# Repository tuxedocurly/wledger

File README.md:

<div align="center">

</div>

> **The Ultimate Inventory Management System for Makers.**
> *Organize your electronic components and find them instantly with WLED.*

Check out the official WLEDger documentation site [here](https://tuxedocurly.github.io/wledger/)
## What is WLEDger?

WLEDger (WLED + Ledger) is a modern, high-performance inventory system designed specifically for electronics hobbyists, makers, and labs. It solves the problem of "I know I have this part, but where is it?" by integrating with **WLED** controllers.

When you search for a component, WLEDger doesn't just tell you "Bin A1" — **it lights up the specific bin on your storage rack.**

<details>
<summary><strong>Why I Made WLEDger</strong></summary>
I have hundreds of electronic components in my lab. I couldn't remember what parts I had or where they were stored, leading to over-buying and under-utilizing. I wanted a system that solved these problems and got me back to doing what I love: making!
<br><br>
Existing tools were expensive, closed source or lacking in features/WLED integration. WLEDger bridges these gaps, providing a purpose-built, open source solution for the physical reality of a maker's workshop.
</details>

---

## Core Features

### Visual LED Locating System

Connect your WLED-powered LED strips or matrices to your storage.

- **Visual Locate:** Click "Locate" on a part, and its bin glows instantly.
- **Grid Painter:** Use the visual Grid Painter tool to easily map LEDs to bins using Matrix, Strip, or Compound layouts.
- **Walls / Dashboards:** Organize your containers and controllers into customizable "Walls" for a clean, organized dashboard view.
- **Stock Status Colors:** Configure different colors for "Locate", "In Stock", "Low Stock", and "Critical".

### Powerful Inventory Management

- **Fast Search:** Instant results using SQLite FTS5 (Full-Text Search).
- **Barcode Scanning:** Built-in support for scanning parts via your phone's camera.
- **Rich Data:** Store datasheets (PDFs), images, supplier links, and cost data.
- **Tagging:** Organize parts with flexible tagging.

### LLM Prompt Templates

Don't let your parts gather dust. Copy the prompt. paste it into your favorite LLM, and get inspired or informed about your inventory.

WLEDger comes with some great default prompts to get you started.

- **Project Ideas:** High quality project ideas to inpsire you to build with your *current* inventory.
- **Integration Guides:** Quick guidance on how to use your parts in a real circuit.
- **Learning Paths:** Curriculum based on the hardware you own to learn new skills.

### Enterprise-Grade Usability

- **Role-Based Access Control:** Admin, Editor, viewer, and (optional) Guest roles.
- **Audit Logging:** Track every change, stock adjustment, and deletion.
- **Responsive Design:** Designed with desktop and mobile in mind.

### Bulk Import, Backup, and Restore

Flexibility in how you manage your parts, and the data you create in WLEDger.

- **Bulk Import:** Import all your parts at once! No UI clickin' required.
- **Backup:** Easily backup all your data. Exports include all your images, docs, and part info in a human-readable format.
- **Restore:** Restore your database from a backup in a single click.

---

## The Tech Stack

WLEDger V2 has been written for performance, type safety, and extensibility.

- **Backend:** [Go](https://go.dev/) (1.25+) - Fast, compiled, and robust.
- **Database:** [SQLite](https://www.sqlite.org/) + `sqlc` + `goose` - Zero-config, reliable storage with type-safe queries and versioned migrations.
- **Frontend:** [Templ](https://templ.guide/) + [HTMX](https://htmx.org/) - Server-side rendering with SPA-like interactivity.
- **Interactivity:** [Alpine.js](https://alpinejs.dev/) - Lightweight JavaScript for UI state.
- **Styling:** [Tailwind CSS v4](https://tailwindcss.com/) + [DaisyUI v5](https://daisyui.com/).
- **Hardware:** [WLED](https://kno.wled.ge/) - The gold standard for controlling LEDs.

---

## Install WLEDger

### Option 1: Docker (Recommended)

The easiest way to run WLEDger is via Docker.

1. Create a directory for your WLEDger data: `mkdir wledger && cd wledger && mkdir data uploads logs`

2. Inside this folder, create a file named `docker-compose.yaml` with the following contents:

```yaml
services:
  wledger:
    # Format: user/repository:tag
    image: tuxedomakes/wledger:latest

    # A custom name for the container instance.
    container_name: wledger

    ports:
      # Maps ports in the format "HOST:CONTAINER"
      - "8080:8080"

    volumes:
      # Maps files in the format "HOST_PATH:CONTAINER_PATH"
      - ./data:/wledger/data
      - ./uploads:/wledger/app/uploads
      - ./logs:/wledger/app/logs

    # Restart policy
    restart: unless-stopped
```

3. Run the following command to start the container:

```BASH
docker compose up -d
```

Visit `http://localhost:8080` to see the WLEDger UI.
>Tip: Save the website as a shortcut on Android or iOS for quick access!

### Option 2: Build from Source

**Prerequisites:**

- **Go:** Version 1.25+
- **Node.js:** Version 23+ (for running `npm`)
- **Make:** A `make` compatible command line tool.

These tools are required for code generation, dependency management, and running the application.

```bash
# 1. Clone the repository
git clone https://github.com/tuxedocurly/wledger.git
cd wledger

# 2. Install dependencies
# This will install the required Go tools and npm packages.
make install_dependencies

# 3. Build the binary
make build

# 4. Run the application
./bin/wledger
```

### Development

WLEDger uses `Templ` for live reloading and `make` for task orchestration.

```bash
make dev
```

This will start:

- Go server (with Templ watcher)
- Templ + Go change watcher
- Tailwind CSS watcher

---

## UI Screenshots

| Dashboard | Inventory |
| :---: | :---: |
|  |  |

| Part Details | Settings |
| :---: | :---: |
|  |  |

---

## Contributing

Contributions are welcome!

1. Fork the repository.
2. Create a feature branch (`git checkout -b feature/amazing-feature`).
3. Commit your changes.
4. Open a Pull Request.

## License

WLEDger is released under AGPL-3.0-only - see the `LICENSE` file for details.

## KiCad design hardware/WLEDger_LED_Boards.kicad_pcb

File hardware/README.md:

## Hardware Designs for WLEDger

**PCB Status:** Tested Working - 11/20/2025

---

This directory contains open-source hardware (KiCad) files for custom PCBs to help you save time building the physical side of your WLEDger inventory system. It is completely optional (but saves a LOT of assembly time).

### This is Completely Optional!

You **do not** need to fabricate this PCB to use WLEDger. The app works with **any** WLED-compatible setup.

This PCB is simply a **time-saver** and a way to get a cleaner, more robust, and more professional-looking final build without the hassle of hand-wiring 64 individual LEDs.

### What's In This Directory?

* **`8-LED-Strip`**: KiCad project files (`.kicad_pro`, `.kicad_sch`, `.kicad_pcb`) for a simple 8-LED strip.
* **`Gerbers`**: Manufacturing files you can upload directly to a manufacturer, along with a BOM and position file.

### How to Use These Files

1.  **Software:** You will need [KiCad](https://www.kicad.org/), a free and open-source electronics design suite, to open and edit these files.
2.  **Modify:** Open the `.kicad_pro` project to modify the schematic (`.kicad_sch`) and/or PCB layout (`.kicad_pcb`) to fit your needs.
3.  **Fabricate:** You can export the Gerber files from KiCad and send them to any PCB fabrication service (like JLCPCB, PCBWay, OSH Park, etc.) to have them professionally made.

---

### 8-LED PCB "Strip" for 8x8 Bins

This PCB is a simple, chainable 8-LED strip utilizing 5v SK6812 RBG LEDs with a .1uF capacitor on each LED.

#### Purpose & Design

This design was specifically created to fit the spacing requirements of this high quality **[8x8 transperent storage bin organizer](https://amzn.to/4oPHY2U)**.

The PCB is dimensioned to fit behind one row of 8 bins. You can fabricate 8 of these identical strips and chain them (using the `D_IN` and `D_OUT` pads, along with `5V` and `GND` pads) to create a single 64-LED WLED segment that maps perfectly to the 64-bin organizer.

This serves as a **design blueprint**. You are highly encouraged to open the KiCad files and modify them to fit your own specific bin setups or storage containers. The design is simple, so it's a great opportunity to learn a new skill if you aren't already familiar with using EDA software!

#### The DIY Alternative

The WLEDger system works perfectly well by hand-wiring individual LEDs. This is a common and fully supported method:

1.  Get a standard LED strip (like a WS2812B "NeoPixel" strip).
2.  Cut the strip into single-LED segments.
3.  Space the LEDs to match the layout of your bins and stick them onto a backer board (cardboard, plywood... your wall, etc. Get freaky with it)
4.  Solder short wires (e.g., 2-3 inches) to the `+5V`, `GND`, and `D_IN`/`D_OUT` pads to chain them together.

## ❗ Bounty Alert ❗
**If you find an LED strip + storage bin combination whose spacing does not require cutting the LEDs**, please let me know! This would be a huge win for simplicity, and the community. I'll even add your name to the credits for this project (if desired). 

You can reach me @TuxedoMakes on the [TuxedoDevices Discord](https://discord.com/invite/HABg37gjrd), submit an issue, or a create a pull request! 🫶

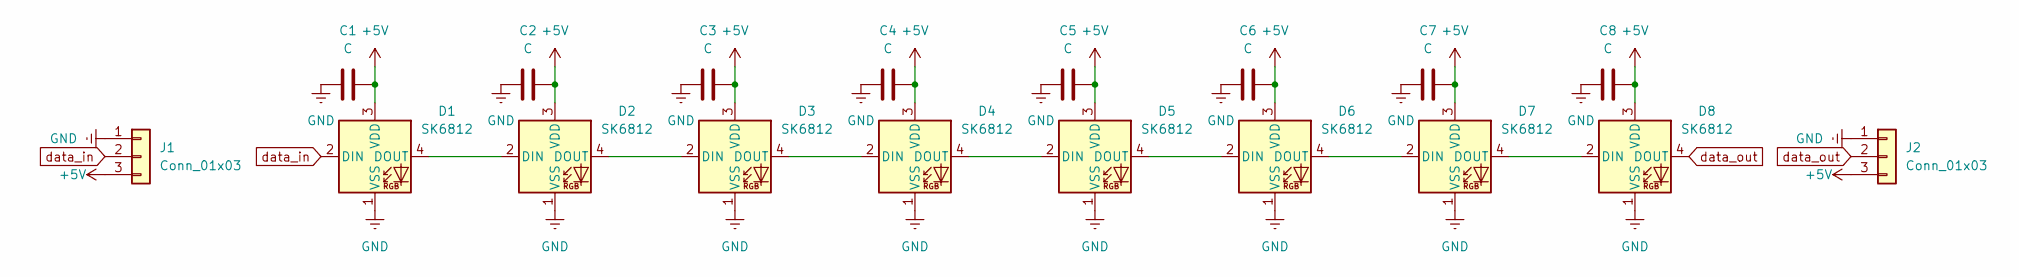
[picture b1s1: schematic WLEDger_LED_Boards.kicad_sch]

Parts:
C1, C2, C3, C4, C5, C6, C7, C8: C; C_0805_2012Metric_Pad1.18x1.45mm_HandSolder
D1, D2, D3, D4, D5, D6, D7, D8: SK6812; LED_SK6812_PLCC4_5.0x5.0mm_P3.2mm
J1, J2: Conn_01x03; SolderWire-0.15sqmm_1x03_P4mm_D0.5mm_OD1.5mm

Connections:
+5V: C1.2, C2.2, C3.2, C4.2, C5.2, C6.2, C7.2, C8.2, D1.3 (VDD), D2.3 (VDD), D3.3 (VDD), D4.3 (VDD), D5.3 (VDD), D6.3 (VDD), D7.3 (VDD), D8.3 (VDD), J1.3, J2.3
GND: C1.1, C2.1, C3.1, C4.1, C5.1, C6.1, C7.1, C8.1, D1.1 (VSS), D2.1 (VSS), D3.1 (VSS), D4.1 (VSS), D5.1 (VSS), D6.1 (VSS), D7.1 (VSS), D8.1 (VSS), J1.1, J2.1
unnamed: D1.4 (DOUT), D2.2 (DIN)
unnamed: D2.4 (DOUT), D3.2 (DIN)
unnamed: D3.4 (DOUT), D4.2 (DIN)
unnamed: D4.4 (DOUT), D5.2 (DIN)
unnamed: D5.4 (DOUT), D6.2 (DIN)
unnamed: D6.4 (DOUT), D7.2 (DIN)
unnamed: D7.4 (DOUT), D8.2 (DIN)
data_in: D1.2 (DIN), J1.2
data_out: D8.4 (DOUT), J2.2

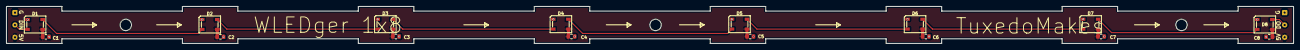
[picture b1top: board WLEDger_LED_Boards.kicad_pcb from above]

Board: 2 copper layers, 417.9 x 12.0 mm, 18 parts (0 on the bottom side), 11 nets.

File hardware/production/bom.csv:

Designator,Footprint,Quantity,Value,LCSC Part #
"C1, C2, C3, C4, C5, C6, C7, C8",0805,8,C,
"D1, D2, D3, D4, D5, D6, D7, D8",LED_SK6812_PLCC4_5.0x5.0mm_P3.2mm,8,SK6812,
"J1, J2",SolderWire-0.15sqmm_1x03_P4mm_D0.5mm_OD1.5mm,2,Conn_01x03,

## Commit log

2025-11-10 Initial commit of WLEDger app
2025-11-10 add developer developer.md updates
2025-11-10 Add README for SQLite database initialization
2025-11-10 Add README for uploaded documents section
2025-11-10 Add README for images directory
2025-11-10 Update documentation links
2025-11-10 Switch to 'just-the-docs' theme for GitHub Pages
2025-11-10 Update _config.yml title to 'WLEDger'
2025-11-10 Update intro text on all pages to reflect the correct project name
2025-11-10 Update _config.yml description
2025-11-10 Update project title for clarity
2025-11-10 update Pages documentation files (index, setup-guide, usage) for clarity
2025-11-14 Refine headings in README.md
    Updated headings in README for consistency and clarity.
2025-11-14 Update setup-guide to adjust recommended LED strip language
2025-11-14 update setup-guide to fix broken links
2025-11-14 Add inspiration tab, action, tests with LLM prompt containing in stock parts.
2025-11-15 Add hardware folder w 8 LED PCB files
2025-11-15 Update header in README for clarity
2025-11-15 Add 'hardware' directory README
2025-11-15 Add hardware-guide.md and update pages links to point to it
2025-11-15 Update README with additional pages links
2025-11-15 Update hardware-guide with more build info
2025-11-15 Add TODOs to top of hardware-guide
2025-11-15 Remove redundant text from developer.md for brevity
2025-11-16 Add WLEDger logo and update README to display it
2025-11-16 Update index.md description and features
2025-11-16 add logo to pages _config.yml
2025-11-16 add favicon to assets folder
2025-11-16 replace .png favicon with .ico favicon
2025-11-20 Refactor project structure to standard go layout
2025-11-20 Refactor tests and move them to the correct directories. All tests passing
2025-11-20 Add backup & restore functionality for DB in settings. Update pages to reflect this change.
2025-11-20 Update Settings page to allow bins section to scroll vertically. Add custom CSS, as pico.css does not support vertical table scrolling yet
2025-11-20 Update hardware README to show that PCBs have been tested and working as expected.
2025-11-20 Add TODO in handlers.go for future refactor of the monolithic handler structure
2025-11-20 Add bin migration feature for controllers. In the event of hardware failure, this allows users to swap bins from one controller to another without having to reconfigure everything.
2025-11-20 feat: Add controller editing, bin migration, and orphan detection
    This update implements a complete lifecycle management system for WLED controllers and bins.
    Features:
    - Controller Editing: Rename/Change IP inline.
    - Bin Migration: Move bins between controllers.
    - Bin Editing: Fix conflicts and re-assign orphans.
    - UI: Added visual warnings for orphans and overlapping LED indexes.
2025-11-21 Major structural refactor to improve modularity. Feature set reamins the same, organizational structure has changed.
2025-11-21 Add more tests to improve coverage.
2025-11-21 update developer guide to reflect post-refactor structural changes
2025-11-21 Clean up comments, update developer docs
2025-11-21 Add image preview to the inventory homepage
2025-11-21 Add GitHub Actions workflow for Docker build and publish
2025-11-21 Update developer.md to remove visual directory display. The viewing is broken on Pages.
2025-11-21 Add multi-platform support for Docker build
2025-11-22 Refactor Dockerfile
    Updated Dockerfile comments and added UI folder copy.
2025-11-22 fix and issue with SQLite driver crash after restoring .zip backup
2025-11-22 remove unused GetParts stub from handler_test.go
2025-11-22 Fix UI inconsistency when no controllers were added on settings page. Change settings.html colspan from 5 to 6 for Existing Controllers
2025-11-22 Update docker-compose.yml, README, and setup-guide to simplify setup process to use the wledger docker hub image.
2025-11-22 Update README with GIFs of the WLEDger UI
2025-11-22 Fix GIF html on README
2025-11-22 Fix html tags in README
2025-11-22 Fix spelling in README GIF title
2025-11-22 Update Inventory page action buttons to take up less space. They use SVG icons instead
2025-11-22 Update inventory description to clamp text after 2 lines
2025-11-22 Fix data-tooltip being squashed by .btn-icon CSS line height
2025-11-22 Fix tag cleanup button on Settings page.
    This fixes an issue where the page would redirect back to /settings after clicking this button due to it being wrapped in a form. The button is now a normal hx button like everything else, and simply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
2025-11-22 Add WLEDger logo to header. Update README logo.
2025-11-22 Update footer with link to report bugs/features, discord link, and support on Ko-Fi
2025-11-22 Update demo GIFs to reflect UI changes
2025-11-22 Update README with bug, discord, and kofi links
2025-11-23 Small changes to wording on index and dashboard templates
2025-11-23 Add hardware demo gif, remove erroneous property from img tag
2025-11-28 Fix incorrect inventory quantity when searching parts with multiple categories
2025-11-28 Fix failing tests: parts_test.go expected an old http response code, store_test.go did not cleanup DB, causing filelock error
2025-11-28 Update docker-compose.yml to mirror README docker-compose.yml snippet
2025-11-28 Update gitignore to exclude test coverage outputs
2025-11-28 Update gitignore
2025-11-30 Fix bug in controllers.go where LastSeen time was improperly scanned. After zip restore, LastSeen time should now appear properly in settings
2025-12-04 add controller bin filterr to settings page
2025-12-12 update comments
2025-12-13 Deleted main.go
2025-12-15 Revert "Deleted main.go"
    This reverts commit d5872c2710facfae7b8ea9fafa6c12f1697a85b5.
2026-01-04 chore: migrate icons to lucide
2026-01-07 Add localization support for en and es
2026-01-08 Fix minor bugs with localizer, add localization to search_bar component
2026-01-08 Add support for DE, FR, IT, PR-BR, RU, ZH
2026-01-14 deploy: 0da1adfff49791f37c50039ebfa8262c0a8e320e
2026-01-14 deploy: 67c4ed56a98c40d1b821ea5632bbec40215aaf2b
2026-01-14 deploy: 06f4ab320ef3deebbb899aefe0a7ca1f16c49b0a
2026-01-15 deploy: ed51e7b948d5108c3b7c8e0ded35e4233163beb1
2026-01-15 deploy: 0e1edf3559eb0dfd88773bfaedb8342d87074f7a
2026-01-15 deploy: 0f798f3d90e870bc98e63bb91f51a5ac2d9afae9
2026-01-15 Create CNAME
2026-01-15 deploy: f24ea2427f9b24f2a84d65b094cb19fcac71b348
2026-01-15 deploy: 97416ddf8b57d09dbce51d047a4dd80ba48b6daf
2026-01-17 deploy: 3dd4b9e13a2d266599ce4d9c5545c128d97cacd6
2026-01-18 deploy: b5d6a8ee35531d8ee6619cf560437a6efba9c787
2026-01-18 feat(ui): show full part description on hover
2026-01-22 deploy: ca3b93add009c5c33566c67b2520be0fe72a144b
2026-02-17 Added a Clone Part Button
2026-02-17 Updated Tests
